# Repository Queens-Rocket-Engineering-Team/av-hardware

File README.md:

# Avionics Hardware
> 2026-2027 SRAD Avionics Hardware Repository

This repository contains **schematics**, **PCB layouts**, and related **documentation and datasheets** for QRET SRAD Avionics. 
- All ECAD was designed in or transferred to **KiCad 10**.
- Covers **all** avionics systems, including power, propulsion, recovery, telemetry, and shared libraries.
- The **main** branch contains the latest stable hardware that is not currently under active development.
- If you're contributing, please read over the [`Development Standards`](#development-standards) section.
---

## Folder Structure
Avionics systems are organized into root-level directories (e.g., `power/`, `telemetry/`, etc.). 

Each system contains folders per boards and a respective documentation file `README.MD`

Each board follows the structure below:
- `docs`: Board-specific documentation, datasheets, and other reference materials. 
- `symbols`: Board-specific schematic symbols.
- `footprints`: Board-specific PCB footprints.
- `models`: Board-specific component 3D-models.

**Example Structure**
```
av-hardware/
  power/
    README.md
    power-module/
      power-module.kicad_pro
      power-module.kicad_sch
      power-module.kicad_pcb
      docs/
        README.md
        datasheets/
      symbols/
      footprints/
      models/
```

## Development Standards
- **Always** ensure you've fetched and pulled from Git before contributing.
```
git fetch origin
git pull
```
- Keep `main` stable. Never make changes directly on `main`.
- If contributing, use focused, concise, and descriptive branch names and commit messages. Look at standards below.
- Commit changes on your branch frequently, don't leave changes hanging.

### Datasheet Naming Convention
- For ICs and other active components, download and attach the component's datasheet with the following name convention:
`[type]-[part-number].pdf`

For example:
- `ADC-ADS131M04.pdf`
  
### Branches
Contribute by creating a branch.

**Naming Conventions**
- Creating a new board: `dev/<description>`
- Updating or adding a feature to an existing board: `feature/board/<description>`
- Resolving an issue on an existing board: `fix/board/<description>`
- Updating documentation and reference materials: `docs/<description>`

For example:
- `dev/camera-module`
- `feature/power-module/change-buck`
- `fix/lcm/can-trx`

### Commits
Commit messages should be focused, concise, and descriptive. Each commit should represent a single logical change.
- You should try and commit after making a **single change**, rather than committing for several changes at once.

**Examples**
```text
Setup schematic env for camera module
Tune differential pair lengths
Update comms module with new LoRa module
Review updated comms module
```

### Pull Requests
Pull requests should clearly describe the changes being introduced and their purpose.

Before opening a pull request:

- Ensure the branch is up to date with `main`.
- Ensure all work and changes are peer-reviewed in person during meetings or office hours.
- Confirm that no unrelated changes are included.

**Title Convention**

```text
<type/board-name>: <short-description>
```
For example:
```text
feature/power-module: Change buck converter
fix/lcm: Switch to standard CAN transceiver
dev/camera-module: Initial design
docs/gps-antenna: Add images to documentation
```

## Comments
- You will likely encounter different schematic "formats" as you look through this repository. As of 2026, we are pushing the use of **hierarchical sheets** to improve modularity and readability. Previously, schematics were designed on a single, large sheet.

If you're ever unsure about anything, reach out to one us leads!!

---
QRET, 2026-2027

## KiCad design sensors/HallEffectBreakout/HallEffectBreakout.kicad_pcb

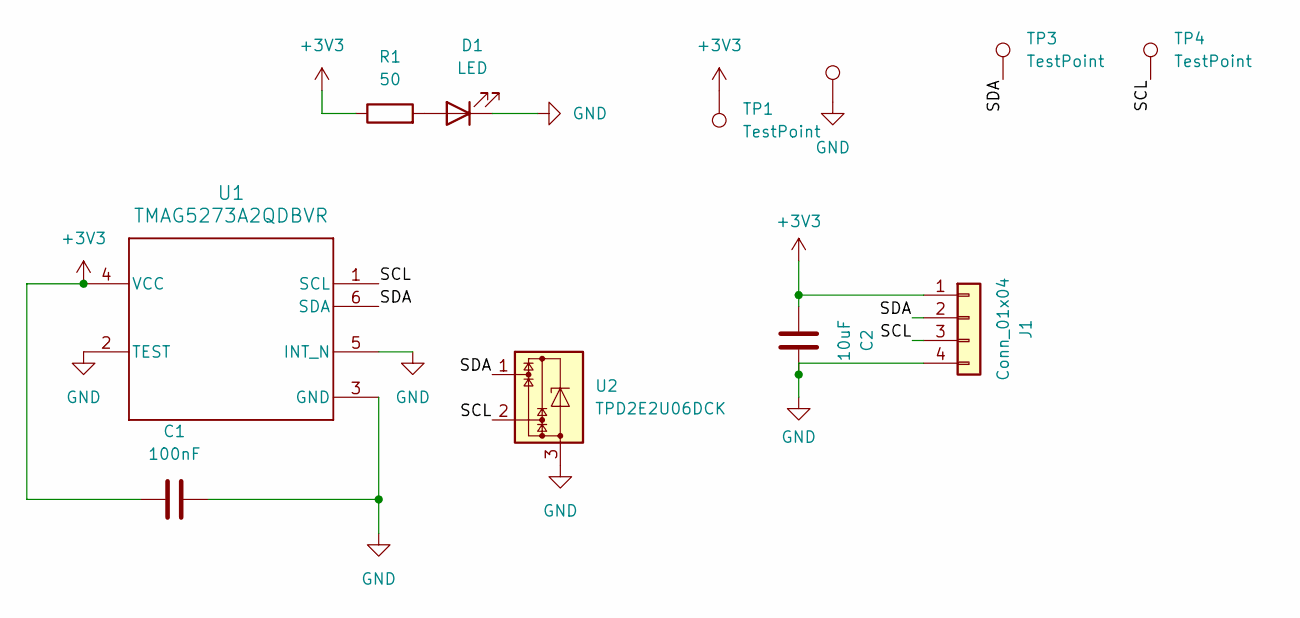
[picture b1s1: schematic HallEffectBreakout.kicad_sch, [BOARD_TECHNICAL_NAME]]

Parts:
C1: 100nF; C_0603_1608Metric_Pad1.08x0.95mm_HandSolder
C2: 10uF; C_0805_2012Metric_Pad1.18x1.45mm_HandSolder
D1: LED; LED_0603_1608Metric_Pad1.05x0.95mm_HandSolder
J1: Conn_01x04; Molex_Nano-Fit_105313-xx04_1x04_P2.50mm_Horizontal
R1: 50; R_0603_1608Metric
TP1, TP2: TestPoint; TestPoint_Pad_1.5x1.5mm
TP3, TP4: TestPoint; TestPoint_THTPad_D1.5mm_Drill0.7mm
U1: TMAG5273A2QDBVR; DBV0006A-MFG
U2: TPD2E2U06DCK; SOT-323_SC-70

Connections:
+3V3: C1.1, C2.1, J1.1, R1.1, TP1.1 (1_1), U1.4 (VCC)
/SCL: J1.3, TP4.1 (1_1), U1.1 (SCL), U2.2
/SDA: J1.2, TP3.1 (1_1), U1.6 (SDA), U2.1
GND: C1.2, C2.2, D1.1 (K), J1.4, TP2.1 (1_1), U1.2 (TEST), U1.3 (GND), U1.5 (INT_N), U2.3
unnamed: D1.2 (A), R1.2

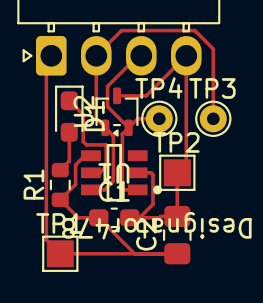
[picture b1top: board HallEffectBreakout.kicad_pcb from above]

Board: 2 copper layers, 11 parts (0 on the bottom side), 5 nets.

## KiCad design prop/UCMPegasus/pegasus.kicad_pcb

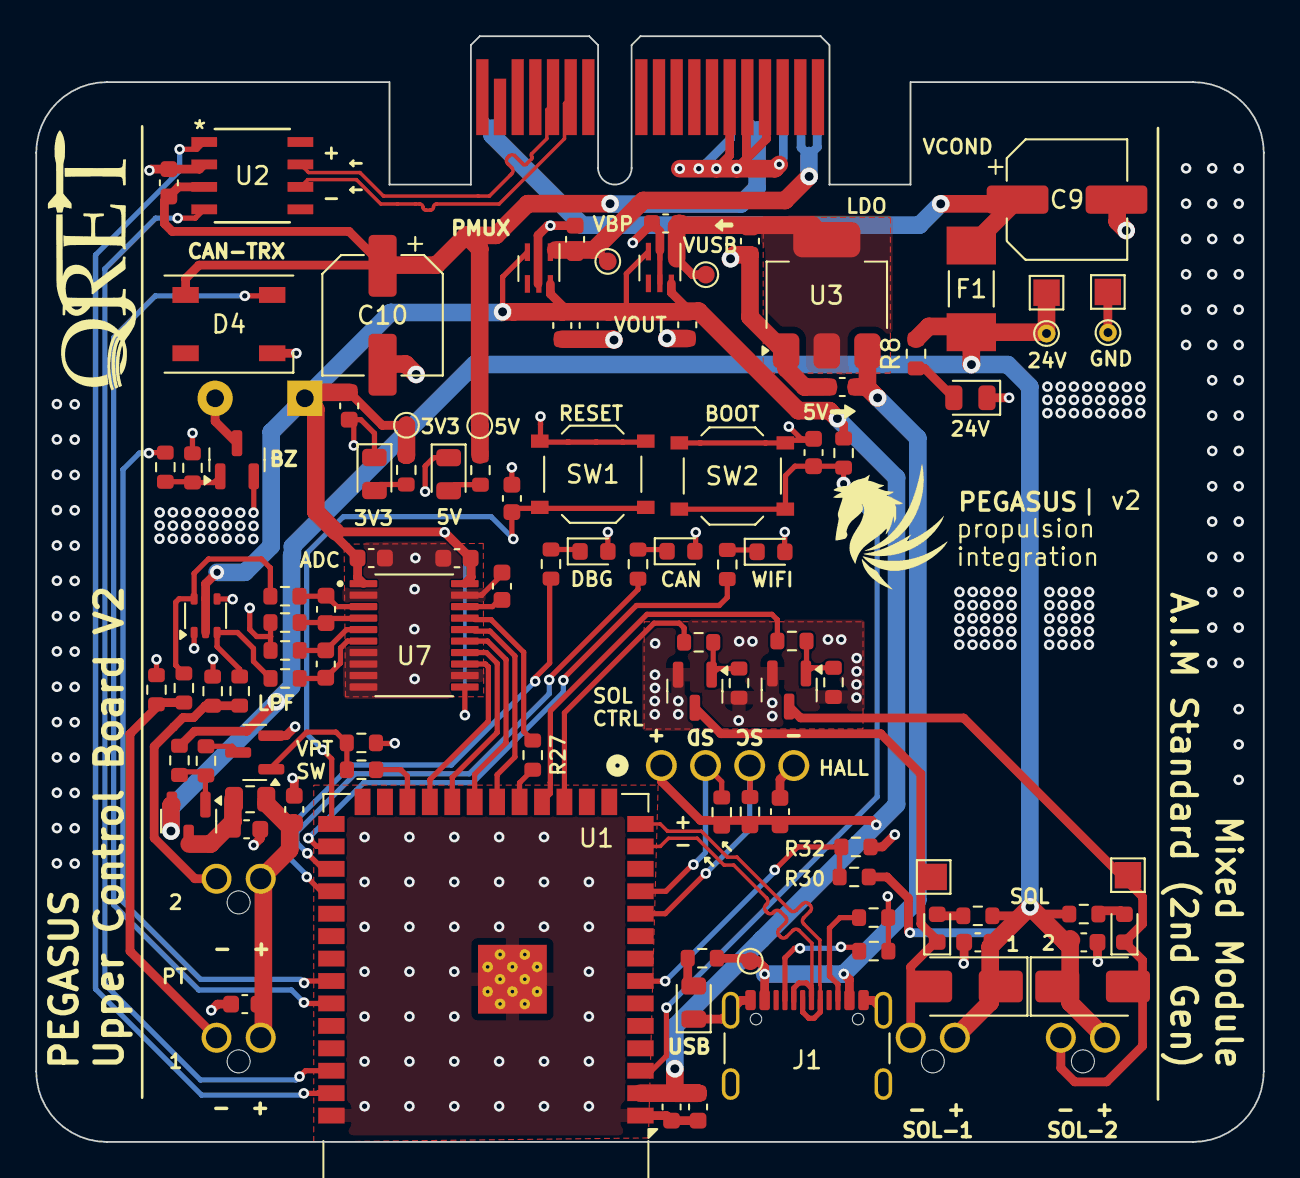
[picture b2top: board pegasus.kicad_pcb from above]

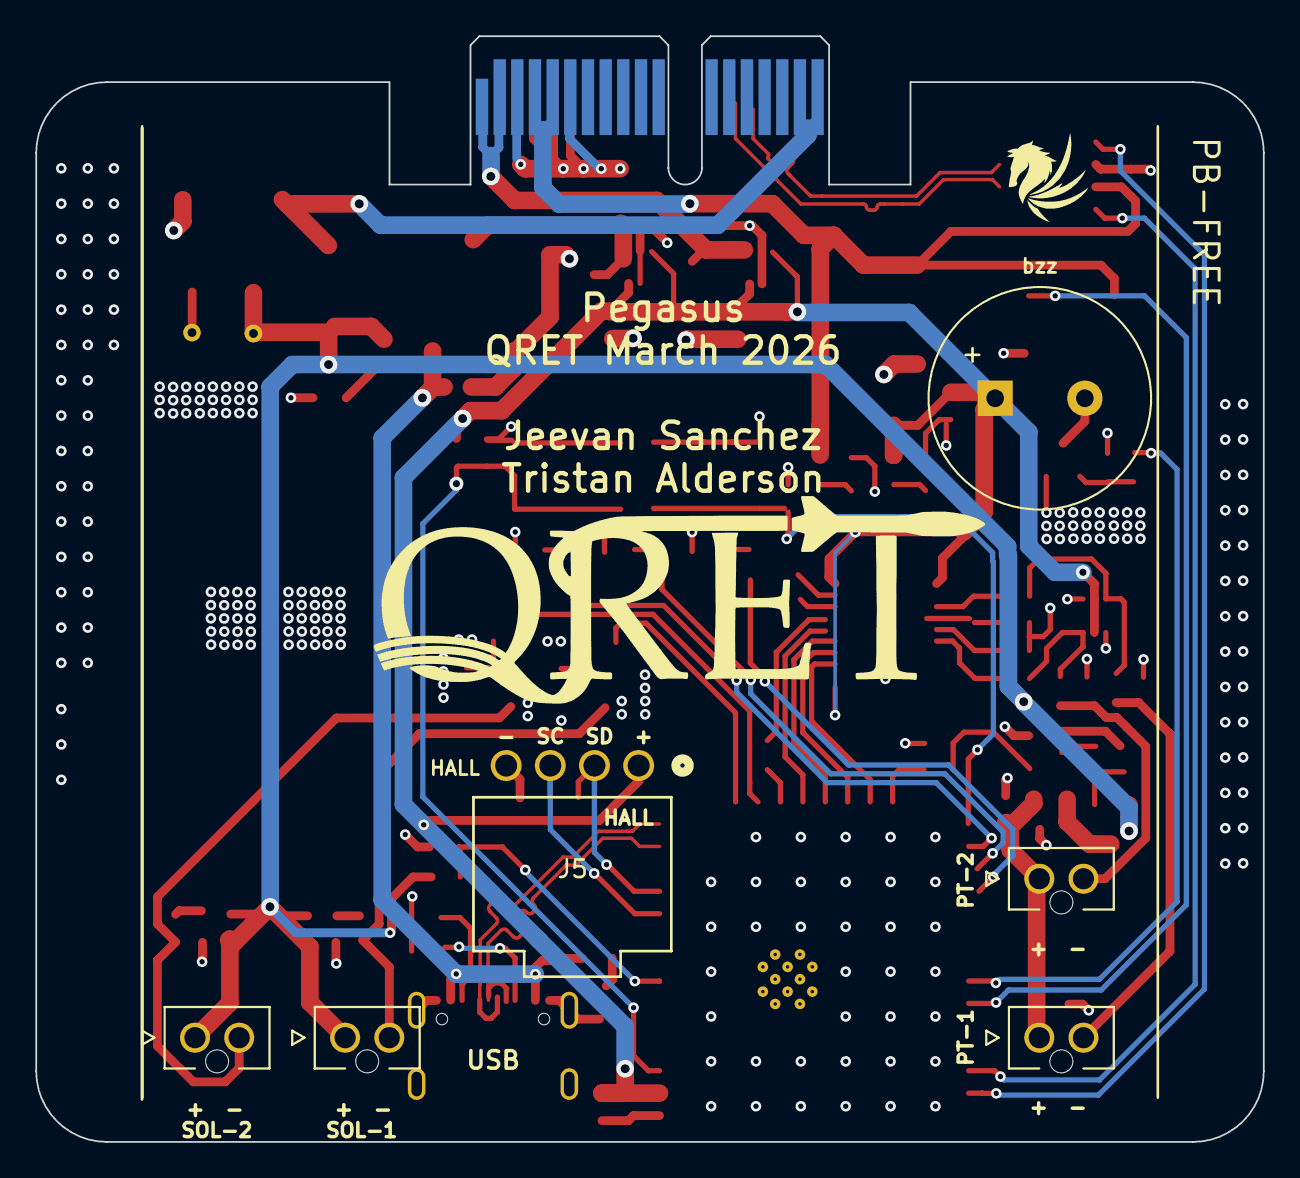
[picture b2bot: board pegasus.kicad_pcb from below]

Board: 4 copper layers, 69.5 x 62.6 mm, 108 parts (6 on the bottom side), 64 nets.

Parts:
BZ1: PS1240P02BT; Buzzer_12.6x9.5RM5.0
C1, C11, C12, C29, C31: 1uF; C_0603_1608Metric
C2, C4, C6, C7, C16, C18, C22, C23: 100nF; C_0603_1608Metric
C3, C5, C8, C14, C17: 10uF; C_0603_1608Metric
C9: 100uF; CP_Elec_6.3x5.9
C10: 100uF 16V; CP_Elec_6.3x5.9
C13, C24: 0.1uF; C_0603_1608Metric
C15: 1nF; C_0603_1608Metric
C25, C26: 10nF; C_0603_1608Metric
C30: 220 nF; C_0603_1608Metric
D1: FAULT_LED (RED); LED_0603_1608Metric
D2: CAN_LED (WHT); LED_0603_1608Metric
D3: WIFI_LED (WHT); LED_0603_1608Metric
D4: SYS_LED_WS2812B; LED_WS2812B_PLCC4_5.0x5.0mm_P3.2mm
D5: PWR_3V3_LED (GRN); LED_0805_2012Metric
D6: PWR_24V_LED (GRN); LED_0805_2012Metric
D7: PWR_5V_LED (GRN); LED_0805_2012Metric
D8: USB_LED (GRN); LED_0805_2012Metric
D9: SOL2_LED (WHT); LED_0603_1608Metric
D10: SOL1_LED (WHT); LED_0603_1608Metric
D11, D12: SS34; D_SMA
D13: BAV199DW; SOT-363_SC-70-6
F1: Fuse; FUSC6125X279N
FB1: 100R; R_0805_2012Metric
J1: USB_C_Female_USB2_Small; USB_C_Receptacle_GCT_USB4105-xx-A_16P_TopMnt_Horizontal
J2: Stack Male Edge Connector; BUS_PCIexpress_x1
J3, J4: SOL_CONN; MOLEX_1053091102
J5: HALL-1; CONN_SD-105313-100_04_MOL
J6, J7: PT; MOLEX_1053091102
Q1, Q2: AO3400A; SOT-23
Q4, Q5: 2N7002; SOT-23
R1, R23, R28, R32, R38: 10k; R_0603_1608Metric
R2: 680; R_0603_1608Metric
R3, R4: 270; R_0603_1608Metric
R5, R6: 5.1k; R_0603_1608Metric
R7: 3.3k; R_0603_1608Metric
R8, R15, R16: 12k; R_0603_1608Metric
R9, R29, R37: 6.2k; R_0603_1608Metric
R10, R11, R13, R19, R31, R39: 200; R_0603_1608Metric
R12, R14, R30: 100k; R_0603_1608Metric
R17, R20: 62; R_0603_1608Metric
R18, R26: 1k; R_0603_1608Metric
R21, R22: 2.2k; R_0603_1608Metric
R24, R25: 1.2k; R_0603_1608Metric
R27: 33; R_0603_1608Metric
SW1: SW_ESP_BOOT_MODE; SW_Push_1P1T_XKB_TS-1187A
SW2: SW_ESP_RESET; SW_Push_1P1T_XKB_TS-1187A
TP1: 5V_USB; TestPoint_Pad_D1.0mm
TP2: 3V3-TP; TestPoint_Pad_D1.0mm
TP3: 24V-TP-P; TestPoint_Pad_1.5x1.5mm
TP4: 5V-TP; TestPoint_Pad_D1.0mm
TP5: GND-TP-P; TestPoint_Pad_1.5x1.5mm
TP6: 3V3_BP; TestPoint_Pad_D1.0mm
TP7: GND-TP-H; TestPoint_THTPad_D1.0mm_Drill0.5mm
TP8: VALVE2_OUT_TP; TestPoint_Pad_1.5x1.5mm
TP9: 3V3_USB; TestPoint_Pad_D1.0mm
TP10: VALVE1_OUT_TP; TestPoint_Pad_1.5x1.5mm
TP11: 24V-TP-H; TestPoint_THTPad_D1.0mm_Drill0.5mm
U1: ESP32-S3-WROOM-1-N16; ESP32-S3-WROOM-1
U2: TCAN1051HGVDR; SOIC_1044BDR_TEX
U3: AMS1117-3.3; SOT-223-3_TabPin2
U4, U5: ID_LM66100DCKR; SC-70-6
U7: ADC_ADS131M04IPWR; SOP65P640X120-20N
U9: DMP4065S-7; SOT-23

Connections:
5V_USB: C14.1, J1.A4 (VBUS), J1.A9 (VBUS), J1.B4 (VBUS), J1.B9 (VBUS), R29.1, TP1.1, U3.3 (VI)
24V_SENSE: R30.2, R32.2, U1.7 (IO7)
+3V3: BZ1.1 (+), C2.1, C3.1, C15.1, C16.1, C17.1, C22.2, C23.1, C29.2, C31.2, D13.2 (K2), D13.5 (K4), J5.1, R1.1, R7.2, R21.2, R22.1, TP2.1, U1.2 (3V3), U4.3 (*CE), U4.6 (VOUT), U5.3 (*CE), U5.6 (VOUT), U7.1 (AVDD), U7.11 (~SYNC/~RESET), U7.20 (DVDD)
+5V: C6.2, C10.1, D4.1 (VDD), J2.A4 (5.0V_A), J2.A5 (5.0V_A), R9.2, TP4.1, U2.3 (VCC)
+24V: C7.1, C18.1, D11.1 (K), D12.1 (K), F1.1, J3.1, J4.1, R8.2, R15.2, R16.2, R30.1, R37.2, TP3.1, TP11.1, U9.2 (S)
+24V_BP: C9.1, F1.2, J2.A17 (24V_A), J2.A18 (24V_A)
/ESP32-S3 Breakout Circuitry/BUZZ_EN: R10.2, U1.34 (IO41)
/ESP32-S3 Breakout Circuitry/CAN_LED: R3.1, U1.29 (IO36)
/ESP32-S3 Breakout Circuitry/CAN_RX: U1.38 (IO2), U2.4 (RXD)
/ESP32-S3 Breakout Circuitry/CAN_TX: U1.39 (IO1), U2.1 (TXD)
/ESP32-S3 Breakout Circuitry/DEBUG_LED: R2.1, U1.30 (IO37)
/ESP32-S3 Breakout Circuitry/ESP32_EN: C1.1, R1.2, SW2.2, U1.3 (EN)
/ESP32-S3 Breakout Circuitry/ESP32_IO0: C4.2, SW1.2, U1.27 (IO0)
/ESP32-S3 Breakout Circuitry/RGB_DATAIN: D4.4 (DIN), U1.35 (IO42)
/ESP32-S3 Breakout Circuitry/USB_N: J1.A7 (D-), J1.B7 (D-), U1.13 (USB_D-)
/ESP32-S3 Breakout Circuitry/USB_P: J1.A6 (D+), J1.B6 (D+), U1.14 (USB_D+)
/ESP32-S3 Breakout Circuitry/WIFI_LED: R4.1, U1.28 (IO35)
/Power Circuitry/3V3_BP: C11.2, J2.A1 (3.3V_A), J2.A2 (3.3V_A), TP6.1, U4.1 (VIN)
/Power Circuitry/3V3_USB: C5.1, C12.1, TP9.1, U3.2 (VO), U5.1 (VIN)
/Sensing Circuitry/PT1_CLAMPED: C25.2, R19.1, U7.3 (AIN0P)
/Sensing Circuitry/PT2_CLAMPED: C26.2, R31.1, U7.6 (AIN1P)
ADC_CLK: R27.1, U7.17 (CLKIN)
ADC_DRDY: U1.23 (IO21), U7.13 (~DRDY)
ADC_MISO: U1.21 (IO13), U7.15 (DOUT)
ADC_MOSI: U1.20 (IO12), U7.16 (DIN)
ADC_SCLK: U1.22 (IO14), U7.14 (SCLK)
CAN_N: J2.B13 (CAN_L), U2.6 (CANL)
CAN_P: J2.B14 (CAN_H), U2.7 (CANH)
GND: C1.2, C2.2, C3.2, C4.1, C5.2, C6.1, C7.2, C8.2, C9.2, C10.2, C11.1, C12.2, C13.2, C14.2, C15.2, C16.2, C17.2, C18.2, C22.1, C23.2, C24.2, C29.1, C30.2, C31.1, D1.2 (A), D2.2 (A), D3.2 (A), D4.3 (VSS), D5.1 (K), D6.1 (K), D7.1 (K), D8.1 (K), D13.1 (A1), D13.4 (A3), J1.A1 (GND), J1.A12 (GND), J1.B1 (GND), J1.B12 (GND), J1.S1 (SHIELD), J2.A3 (GND_A), J2.A6 (GND_A), J2.B4 (GND_A), J2.B5 (GND_A), J2.B6 (GND_A), J5.4, Q1.2 (S), Q2.2 (S), Q4.2 (S), Q5.2 (S), R5.2, R6.2, R12.1, R14.1, R17.1, R20.1, R24.1, R25.1, R28.1, R32.1, R38.1, SW1.1, SW2.1, TP5.1, TP7.1, U1.1 (GND), U1.40 (GND), U1.41 (GND), U2.2 (GND), U3.1 (ADJ), U4.2 (GND), U4.5 (ST), U5.2 (GND), U5.5 (ST), U7.2 (AGND), U7.7 (AIN2P), U7.8 (AIN2N), U7.9 (AIN3N), U7.10 (AIN3P), U7.12 (~CS), U7.19 (DGND)
HALL_SCL: J5.3, R22.2, U1.10 (IO17)
HALL_SDA: J5.2, R21.1, U1.11 (IO18)
unnamed: BZ1.2 (-), Q4.3 (D)
unnamed: D1.1 (K), R2.2
unnamed: D2.1 (K), R3.2
unnamed: D3.1 (K), R4.2
unnamed: D5.2 (A), R7.1
unnamed: D6.2 (A), R8.1
unnamed: D7.2 (A), R9.1
unnamed: D8.2 (A), R29.2
unnamed: D9.2 (A), R15.1
unnamed: D10.2 (A), R16.1
unnamed: D13.6 (K3A4), R18.2, R19.2
unnamed: D13.3 (K1A2), R26.2, R31.2
unnamed: J1.A5 (CC1), R5.1
unnamed: J1.B5 (CC2), R6.1
unnamed: J6.2, R17.2, R18.1
unnamed: J7.2, R20.2, R26.1
unnamed: Q1.1 (G), R11.1, R12.2
unnamed: Q2.1 (G), R13.1, R14.2
unnamed: Q4.1 (G), R10.1, R28.2
unnamed: Q5.3 (D), R23.1
unnamed: Q5.1 (G), R38.2, R39.2
unnamed: R27.2, U1.19 (IO11)
unnamed: C25.1, R24.2, U7.4 (AIN0N)
unnamed: C26.1, R25.2, U7.5 (AIN1N)
unnamed: C30.1, U7.18 (CAP)
unnamed: C8.1, FB1.1, U9.3 (D)
unnamed: R23.2, R37.1, U9.1 (G)
SOL1_EN: R11.2, U1.17 (IO9)
SOL1_RET: D10.1 (K), D11.2 (A), J3.2, Q1.3 (D), TP10.1
SOL2_EN: R13.2, U1.18 (IO10)
SOL2_RET: D9.1 (K), D12.2 (A), J4.2, Q2.3 (D), TP8.1
VPT: C13.1, C24.1, FB1.2, J6.1, J7.1
VPT_EN: R39.1, U1.24 (IO47)

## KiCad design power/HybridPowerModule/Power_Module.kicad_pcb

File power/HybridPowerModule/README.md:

# [Board Name]

## Overview

Brief description of the board, its purpose, and its role within the [System Name] system.

## Electrical Characteristics

| Parameter | Value |
|-----------|-------|

## Specifications

### MCU

- **Part:** 
- **Architecture:** 
- **Clock:** 
- **Memory:** 

### Communications

### Other/Peripherals

- **Sensors:** 
- **Storage:** 
- **Connectors:** 

## System Partitioning
Brief, abstract overviews of the different subsystems across the board. Think of the board as the main system.
- A subsytem could be the board's power, the controlling cirucit of a main peripheral, etc.

### [Partition Name]

Description of the subsytem and its function.

### [Partition Name]

Description of the substeym and its function.

...
## Hardware

### Major Hardware Components

- **[Component]**: Description
...

### Major Circuits

**[Circuit]**
- Description, supporting calculations, snippet of circuit.

## History
- Any relevant information on the board's histroy: issues, etc. 

## Status

**Status:** [Development / Review / Shipped / Assembly / Testing / Validated / ]

**Revision:** [Revision]

## Changelog

### [Revision]
- Description of change | Date
- Description of change | Date
...

---
QRET, 2026-2027

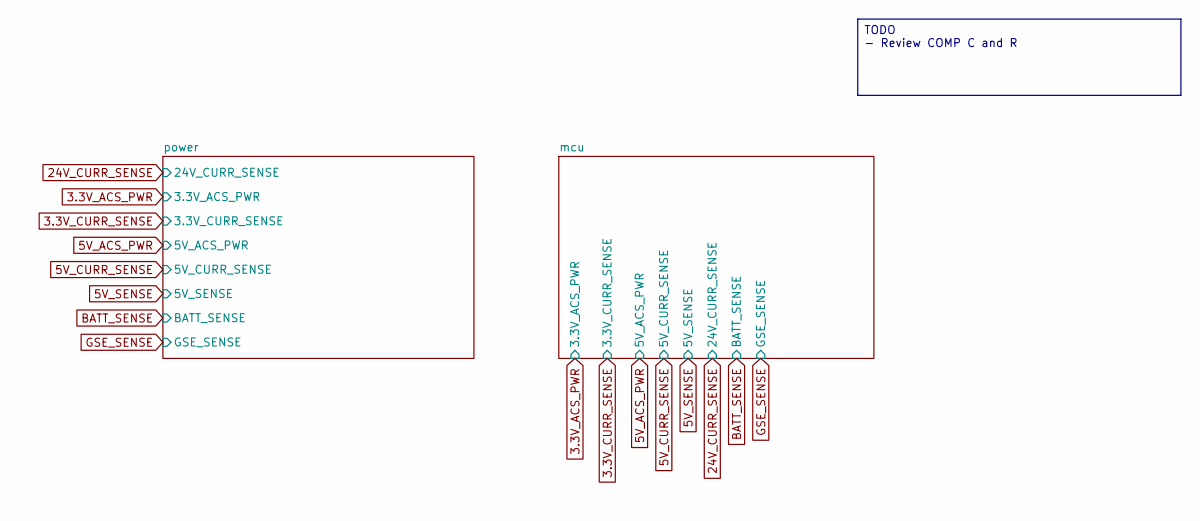
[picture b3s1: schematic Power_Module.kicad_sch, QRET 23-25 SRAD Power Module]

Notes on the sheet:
TODO - Review COMP C and R

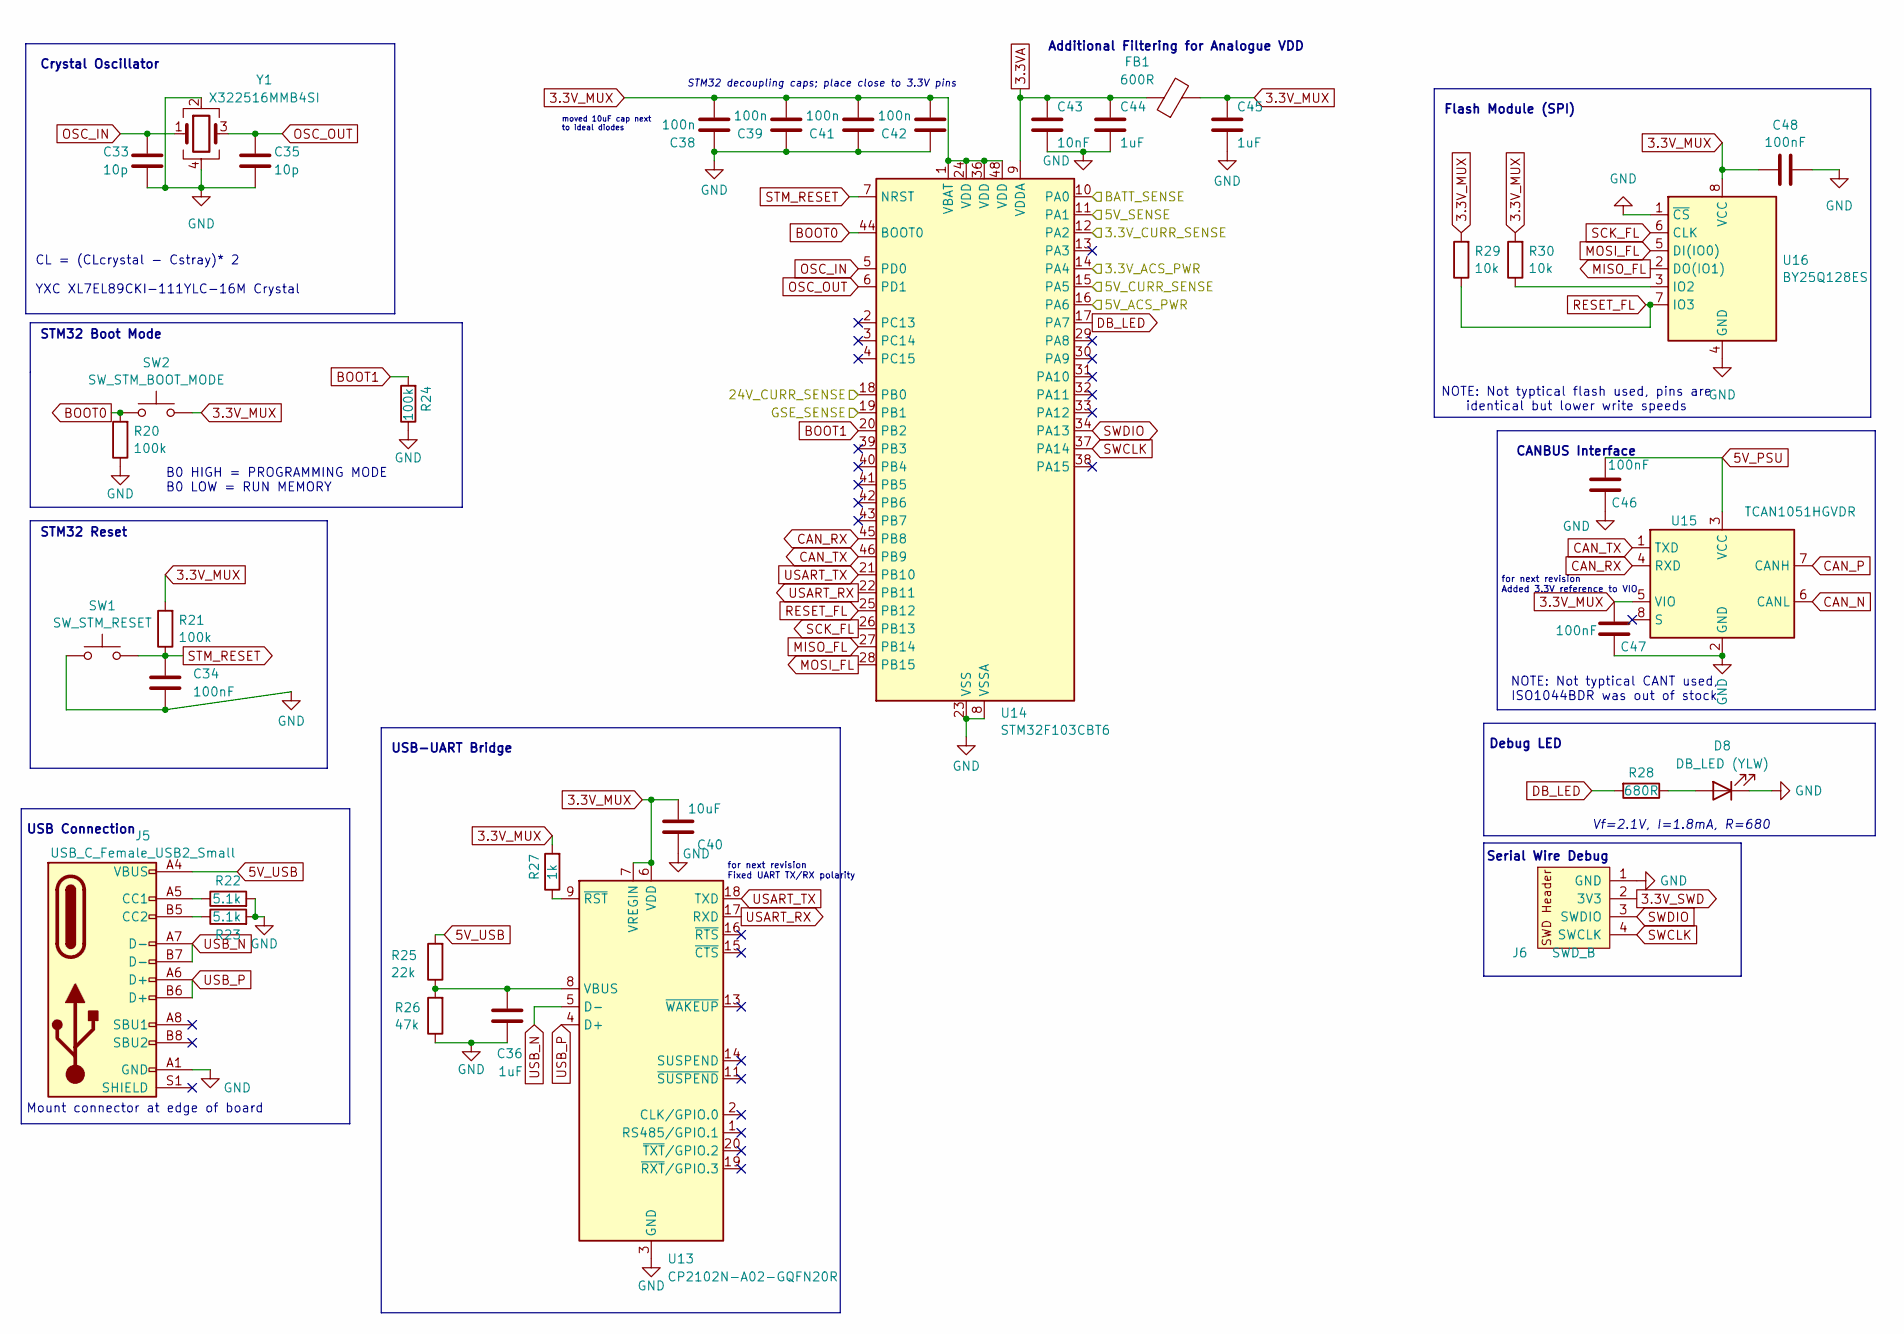
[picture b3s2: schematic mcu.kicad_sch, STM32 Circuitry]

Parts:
C33, C35: 10p; C_0402_1005Metric; LCSC C32949
C34, C46, C47, C48: 100nF; C_0603_1608Metric; LCSC C14663
C36, C44, C45: 1uF; C_0603_1608Metric; LCSC C15849
C38, C39, C41, C42: 100n; C_0402_1005Metric; LCSC C1525
C40: 10uF; C_0603_1608Metric; LCSC C96446
C43: 10nF; C_0603_1608Metric; LCSC C57112
D8: DB_LED (YLW); LED_0603_1608Metric; LCSC C2290
FB1: 600R; L_0603_1608Metric; LCSC C1002
J5: USB_C_Female_USB2_Small; USB_C_DB-108PWB; LCSC C5178541
J6: SWD_B; SWD_PinHeader_1x04_P2.54mm_Horizontal_SMD; Digikey 952-3233-ND
R20, R21, R24: 100k; R_0603_1608Metric; LCSC C25803
R22, R23: 5.1k; R_0603_1608Metric; LCSC C23186
R25: 22k; R_0603_1608Metric; LCSC C31850
R26: 47k; R_0603_1608Metric; LCSC C25819
R27: 1k; R_0603_1608Metric; LCSC C21190
R28: 680R; R_0603_1608Metric; LCSC C23228
R29, R30: 10k; R_0603_1608Metric; LCSC C25804
SW1: SW_STM_RESET; SW_Push_1P1T_XKB_TS-1187A; LCSC C318884
SW2: SW_STM_BOOT_MODE; SW_Push_1P1T_XKB_TS-1187A; LCSC C318884
U13: CP2102N-A02-GQFN20R; QFN-20-1EP_3x3mm; LCSC C969913
U14: STM32F103CBT6; LQFP-48_7x7mm_P0.5mm; LCSC C8304
U15: TCAN1051HGVDR; SOIC_1044BDR_TEX; Digikey 296-44225-1-ND
U16: BY25Q128ES; SOIC-8_5.23x5.23mm_P1.27mm; Digikey 5369-BY25Q128ESSIG(R)CT-ND
Y1: X322516MMB4SI; Crystal_SMD_3225-4Pin_3.2x2.5mm; LCSC C13738

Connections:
3.3VA: C43.1, C44.1, FB1.1, U14.9 (VDDA)
3.3V_ACS_PWR: U14.14 (PA4); also elsewhere on the board
3.3V_CURR_SENSE: U14.12 (PA2); also elsewhere on the board
3.3V_MUX: C38.2, C39.2, C40.1, C41.2, C42.2, C45.1, C47.1, C48.1, FB1.2, R21.2, R27.2, R29.2, R30.2, SW2.2, U13.6 (VDD), U13.7 (VREGIN), U14.1 (VBAT), U14.24 (VDD), U14.36 (VDD), U14.48 (VDD), U15.5 (VIO), U16.8 (VCC); also elsewhere on the board
3.3V_SWD: J6.2 (3V3); also elsewhere on the board
5V_ACS_PWR: U14.16 (PA6); also elsewhere on the board
5V_CURR_SENSE: U14.15 (PA5); also elsewhere on the board
5V_PSU: C46.1, U15.3 (VCC); also elsewhere on the board
5V_SENSE: U14.11 (PA1); also elsewhere on the board
5V_USB: J5.A4 (VBUS), J5.A9 (VBUS), J5.B4 (VBUS), J5.B9 (VBUS), R25.2; also elsewhere on the board
24V_CURR_SENSE: U14.18 (PB0); also elsewhere on the board
BATT_SENSE: U14.10 (PA0); also elsewhere on the board
BOOT0: R20.2, SW2.1, U14.44 (BOOT0)
BOOT1: R24.2, U14.20 (PB2)
CAN_N: U15.6 (CANL); also elsewhere on the board
CAN_P: U15.7 (CANH); also elsewhere on the board
CAN_RX: U14.45 (PB8), U15.4 (RXD)
CAN_TX: U14.46 (PB9), U15.1 (TXD)
DB_LED: R28.2, U14.17 (PA7)
GND: C33.2, C34.2, C35.2, C36.1, C38.1, C39.1, C40.2, C41.1, C42.1, C43.2, C44.2, C45.2, C46.2, C47.2, C48.2, D8.1 (K), J5.A1 (GND), J5.A12 (GND), J5.B1 (GND), J5.B12 (GND), J6.1 (GND), R20.1, R22.2, R23.2, R24.1, R26.1, SW1.1, U13.3 (GND), U13.12 (GND), U13.21 (GND), U14.8 (VSSA), U14.23 (VSS), U14.35 (VSS), U14.47 (VSS), U15.2 (GND), U16.1 (~CS), U16.4 (GND), Y1.2, Y1.4; also elsewhere on the board
GSE_SENSE: U14.19 (PB1); also elsewhere on the board
MISO_FL: U14.27 (PB14), U16.2 (DO(IO1))
MOSI_FL: U14.28 (PB15), U16.5 (DI(IO0))
unnamed: D8.2 (A), R28.1
unnamed: J5.A5 (CC1), R22.1
unnamed: J5.B5 (CC2), R23.1
unnamed: C36.2, R25.1, R26.2, U13.8 (VBUS)
unnamed: R27.1, U13.9 (~RST)
unnamed: R30.1, U16.3 (IO2)
OSC_IN: C33.1, U14.5 (PD0), Y1.1
OSC_OUT: C35.1, U14.6 (PD1), Y1.3
RESET_FL: R29.1, U14.25 (PB12), U16.7 (IO3)
SCK_FL: U14.26 (PB13), U16.6 (CLK)
STM_RESET: C34.1, R21.1, SW1.2, U14.7 (NRST)
SWCLK: J6.4 (SWCLK), U14.37 (PA14)
SWDIO: J6.3 (SWDIO), U14.34 (PA13)
USART_RX: U13.17 (RXD), U14.22 (PB11)
USART_TX: U13.18 (TXD), U14.21 (PB10)
USB_N: J5.A7 (D-), J5.B7 (D-), U13.5 (D-)
USB_P: J5.A6 (D+), J5.B6 (D+), U13.4 (D+)

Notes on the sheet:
STM32 Reset
STM32 decoupling caps; place close to 3.3V pins
NOTE: Not typtical CANT used, ISO1044BDR was out of stock
Vf=2.1V, I=1.8mA, R=680
CANBUS Interface
for next revision Fixed UART TX/RX polarity
Flash Module (SPI)
NOTE: Not typtical flash used, pins are identical but lower write speeds
Serial Wire Debug
Debug LED
B0 HIGH = PROGRAMMING MODE B0 LOW = RUN MEMORY
USB-UART Bridge
CL = (CLcrystal - Cstray)* 2 YXC XL7EL89CKI-111YLC-16M Crystal
Mount connector at edge of board
Crystal Oscillator
for next revision Added 3.3V reference to VIO
moved 10uF cap next to ideal diodes
STM32 Boot Mode
USB Connection
Additional Filtering for Analogue VDD
